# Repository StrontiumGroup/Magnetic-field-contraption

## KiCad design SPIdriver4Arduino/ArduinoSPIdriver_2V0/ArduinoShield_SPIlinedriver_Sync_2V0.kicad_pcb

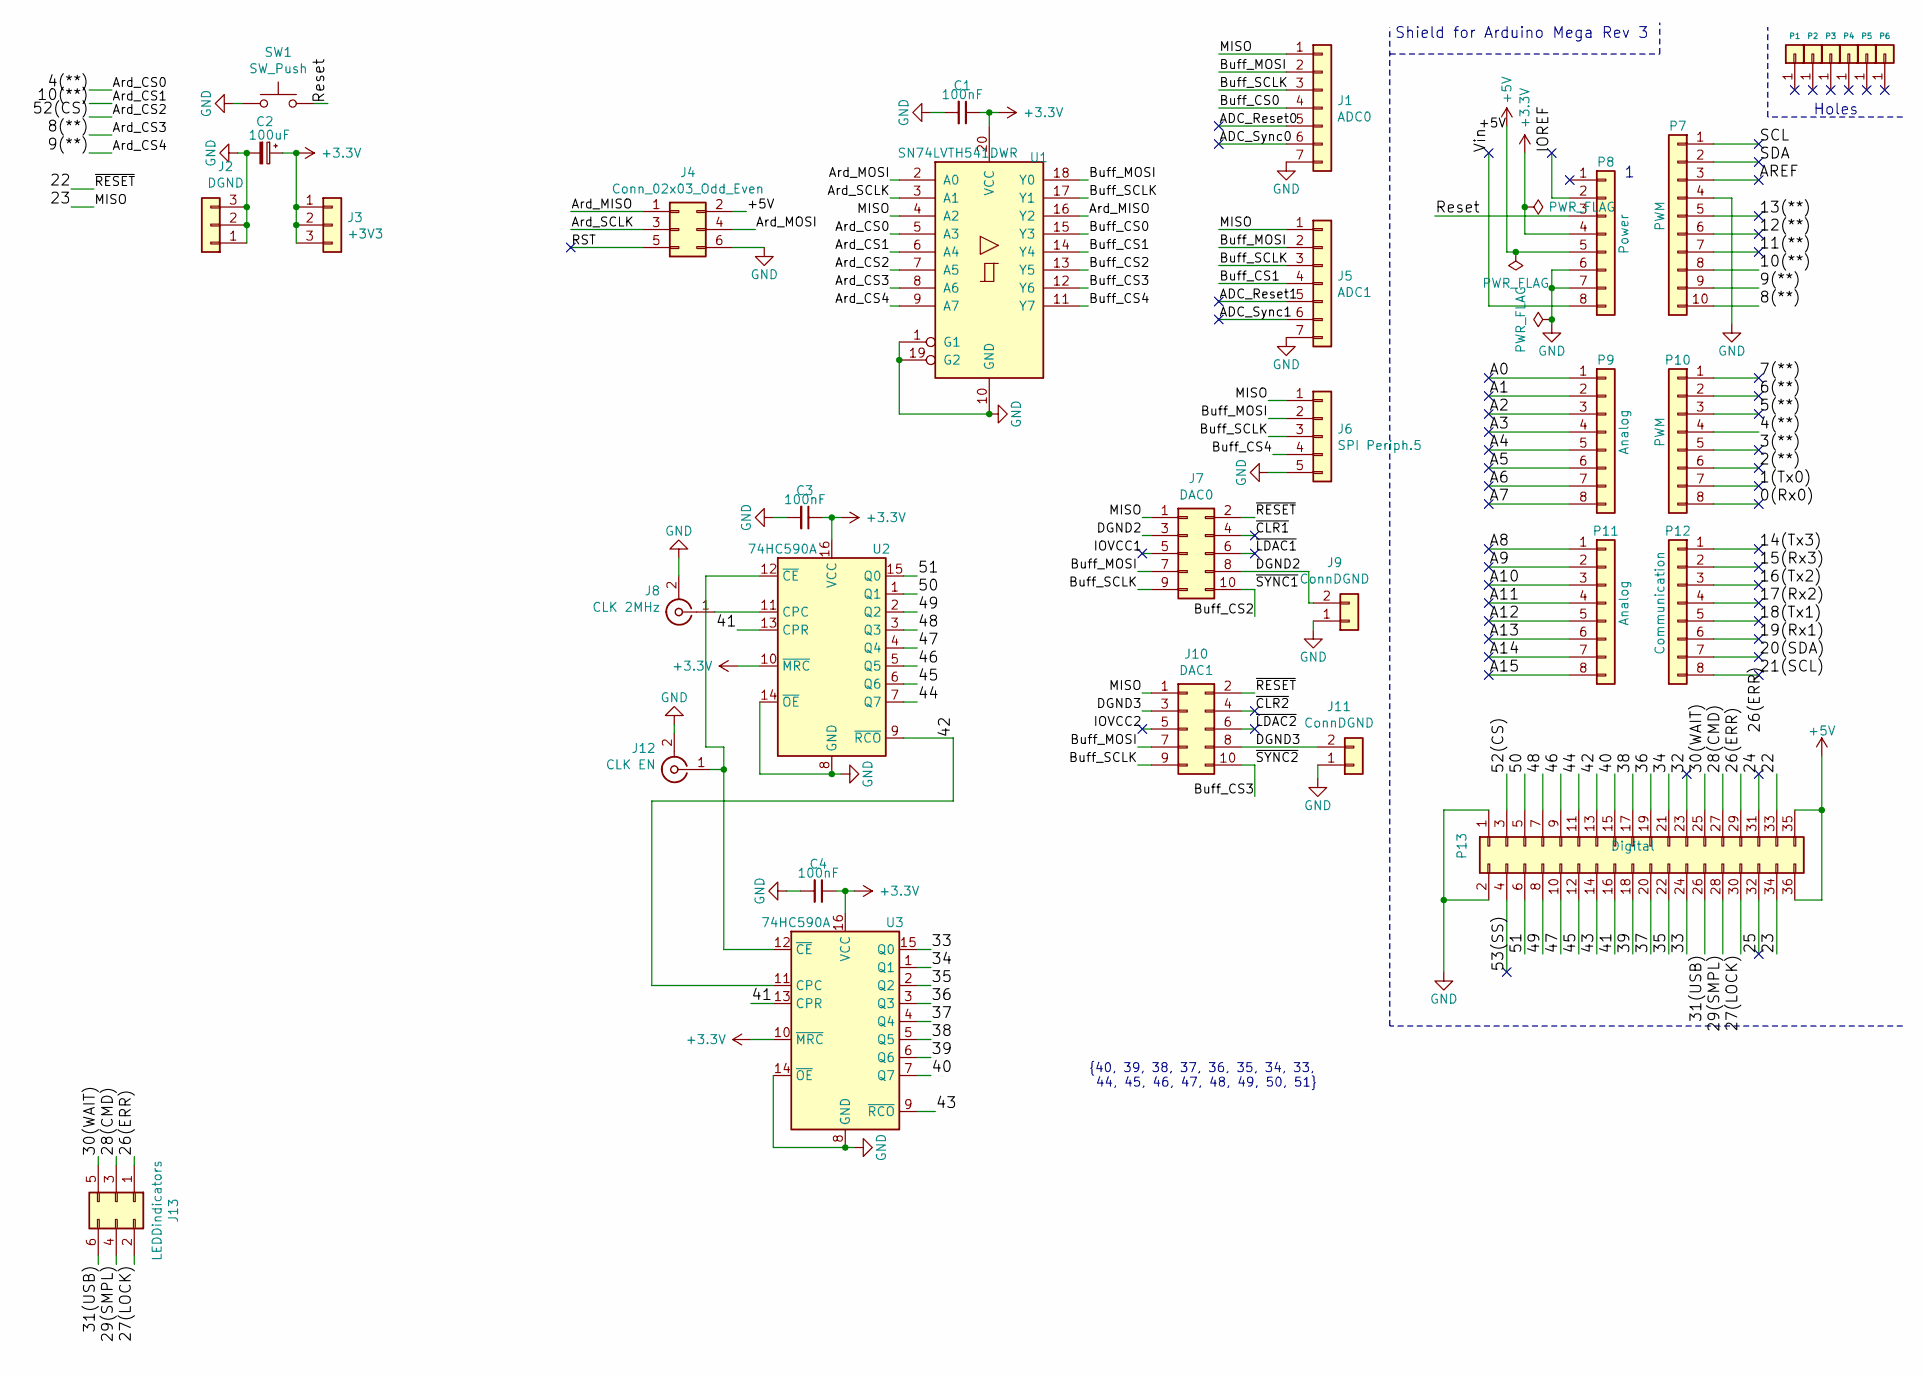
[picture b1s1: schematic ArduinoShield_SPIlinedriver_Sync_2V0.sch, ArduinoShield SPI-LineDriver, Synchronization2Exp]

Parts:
C1, C3, C4: 100nF; C_0805_2012Metric; DigiKey 399-1170-2-ND
C2: 100uF; CP_Radial_D5.0mm_P2.00mm; DigiKey 399-15740-ND
J1: ADC0; Molex_Micro-Latch_53253-0770_1x07_P2.00mm_Vertical; DigiKey WM24307-ND
J2: DGND; PinSocket_1x03_P2.54mm_Vertical
J3: +3V3; PinSocket_1x03_P2.54mm_Vertical
J4: Conn_02x03_Odd_Even; PinSocket_2x03_P2.54mm_Vertical; DigiKey SAM9289-ND
J5: ADC1; Molex_Micro-Latch_53253-0770_1x07_P2.00mm_Vertical; DigiKey WM24307-ND
J6: SPI Periph.5; PinSocket_1x05_P2.54mm_Vertical
J7: DAC0; IDC-Header_2x05_P2.54mm_Vertical; DigiKey WM3478-ND
J8: CLK 2MHz; SMA_Amphenol_132291_Vertical; DigiKey ACX1976-ND
J9, J11: ConnDGND; PinHeader_1x02_P2.54mm_Vertical
J10: DAC1; IDC-Header_2x05_P2.54mm_Vertical; DigiKey WM3478-ND
J12: CLK EN; SMA_Amphenol_132291_Vertical; DigiKey ACX1976-ND
J13: LEDDindicators; IDC-Header_2x03_P2.54mm_Vertical; DigiKey 732-5394-ND
P1, P2, P3, P4, P5, P6: CONN_01X01; Arduino_1pin
P7: PWM; Socket_Strip_Arduino_1x10
P8: Power; Socket_Strip_Arduino_1x08
P9, P11: Analog; Socket_Strip_Arduino_1x08
P10: PWM; Socket_Strip_Arduino_1x08
P12: Communication; Socket_Strip_Arduino_1x08
P13: Digital; Socket_Strip_Arduino_2x18
SW1: SW_Push; SW_SPST_TL3305A; DigiKey LL3301FF065QJ-ND
U1: SN74LVTH541DWR; SOIC-20W_7.5x12.8mm_P1.27mm; DigiKey 296-36417-1-ND
U2, U3: 74HC590A; SOIC-16_3.9x9.9mm_P1.27mm; DigiKey 296-17132-1-ND

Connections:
+3V3: C1.1, C2.1, C3.1, C4.1, J3.1, J3.2, J3.3, P8.4, U1.20 (VCC), U2.10 (~MRC), U2.16 (VCC), U3.10 (~MRC), U3.16 (VCC)
+5V: J4.2, P8.5, P13.35, P13.36
/0(Rx0): P10.8
/1(Tx0): P10.7
/2(**): P10.6
/3(**): P10.5
/4(**): P10.4, U1.5 (A3)
/5(**): P10.3
/6(**): P10.2
/7(**): P10.1
/8(**): P7.10, U1.8 (A6)
/9(**): P7.9, U1.9 (A7)
/10(**): P7.8, U1.6 (A4)
/11(**): P7.7
/12(**): P7.6
/13(**): P7.5
/14(Tx3): P12.1
/15(Rx3): P12.2
/16(Tx2): P12.3
/17(Rx2): P12.4
/18(Tx1): P12.5
/19(Rx1): P12.6
/20(SDA): P12.7
/21(SCL): P12.8
/22: J7.2, J10.2, P13.33
/23: J1.1, J5.1, J6.1, J7.1, J10.1, P13.34, U1.4 (A2)
/24: P13.31
/25: P13.32
/26(ERR): J13.1, P13.29
/27(LOCK): J13.2, P13.30
/28(CMD): J13.3, P13.27
/29(SMPL): J13.4, P13.28
/30(WAIT): J13.5, P13.25
/31(USB): J13.6, P13.26
/32: P13.23
/33: P13.24, U3.15 (Q0)
/34: P13.21, U3.1 (Q1)
/35: P13.22, U3.2 (Q2)
/36: P13.19, U3.3 (Q3)
/37: P13.20, U3.4 (Q4)
/38: P13.17, U3.5 (Q5)
/39: P13.18, U3.6 (Q6)
/40: P13.15, U3.7 (Q7)
/41: P13.16, U2.13 (CPR), U3.13 (CPR)
/42: P13.13, U2.9 (~RCO), U3.11 (CPC)
/43: P13.14, U3.9 (~RCO)
/44: P13.11, U2.7 (Q7)
/45: P13.12, U2.6 (Q6)
/46: P13.9, U2.5 (Q5)
/47: P13.10, U2.4 (Q4)
/48: P13.7, U2.3 (Q3)
/49: P13.8, U2.2 (Q2)
/50: P13.5, U2.1 (Q1)
/51: P13.6, U2.15 (Q0)
/52(CS): P13.3, U1.7 (A5)
/53(SS): P13.4
/A0: P9.1
/A1: P9.2
/A2: P9.3
/A3: P9.4
/A4: P9.5
/A5: P9.6
/A6: P9.7
/A7: P9.8
/A8: P11.1
/A9: P11.2
/A10: P11.3
/A11: P11.4
/A12: P11.5
/A13: P11.6
/A14: P11.7
/A15: P11.8
/ADC_Reset0: J1.5
/ADC_Reset1: J5.5
/ADC_Sync0: J1.6
/ADC_Sync1: J5.6
/AREF: P7.3
/Ard_MISO: J4.1, U1.16 (Y2)
/Ard_MOSI: J4.4, U1.2 (A0)
/Ard_SCLK: J4.3, U1.3 (A1)
/Buff_CS0: J1.4, U1.15 (Y3)
/Buff_CS1: J5.4, U1.14 (Y4)
/Buff_CS2: J7.10, U1.13 (Y5)
/Buff_CS3: J10.10, U1.12 (Y6)
/Buff_CS4: J6.4, U1.11 (Y7)
/Buff_MOSI: J1.2, J5.2, J6.2, J7.7, J10.7, U1.18 (Y0)
/Buff_SCLK: J1.3, J5.3, J6.3, J7.9, J10.9, U1.17 (Y1)
/DGND2: J7.3, J7.8, J9.2
/DGND3: J10.3, J10.8, J11.2
/IOREF: P8.2
/IOVCC1: J7.5
/IOVCC2: J10.5
/RST: J4.5
/Reset: P8.3, SW1.2
/SCL: P7.1
/SDA: P7.2
/Vin: P8.8
/~CLR1: J7.4
/~CLR2: J10.4
/~LDAC1: J7.6
/~LDAC2: J10.6
GND: C1.2, C2.2, C3.2, C4.2, J1.7, J2.1, J2.2, J2.3, J4.6, J5.7, J6.5, J8.2 (Ext), J9.1, J11.1, J12.2 (Ext), P7.4, P8.6, P8.7, P13.1, P13.2, SW1.1, U1.1 (G1), U1.10 (GND), U1.19 (G2), U2.8 (GND), U2.14 (~OE), U3.8 (GND), U3.14 (~OE)
unnamed: J8.1 (In), U2.11 (CPC)
unnamed: J12.1 (In), U2.12 (~CE), U3.12 (~CE)

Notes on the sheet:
Shield for Arduino Mega Rev 3
Holes
{40, 39, 38, 37, 36, 35, 34, 33, 44, 45, 46, 47, 48, 49, 50, 51}

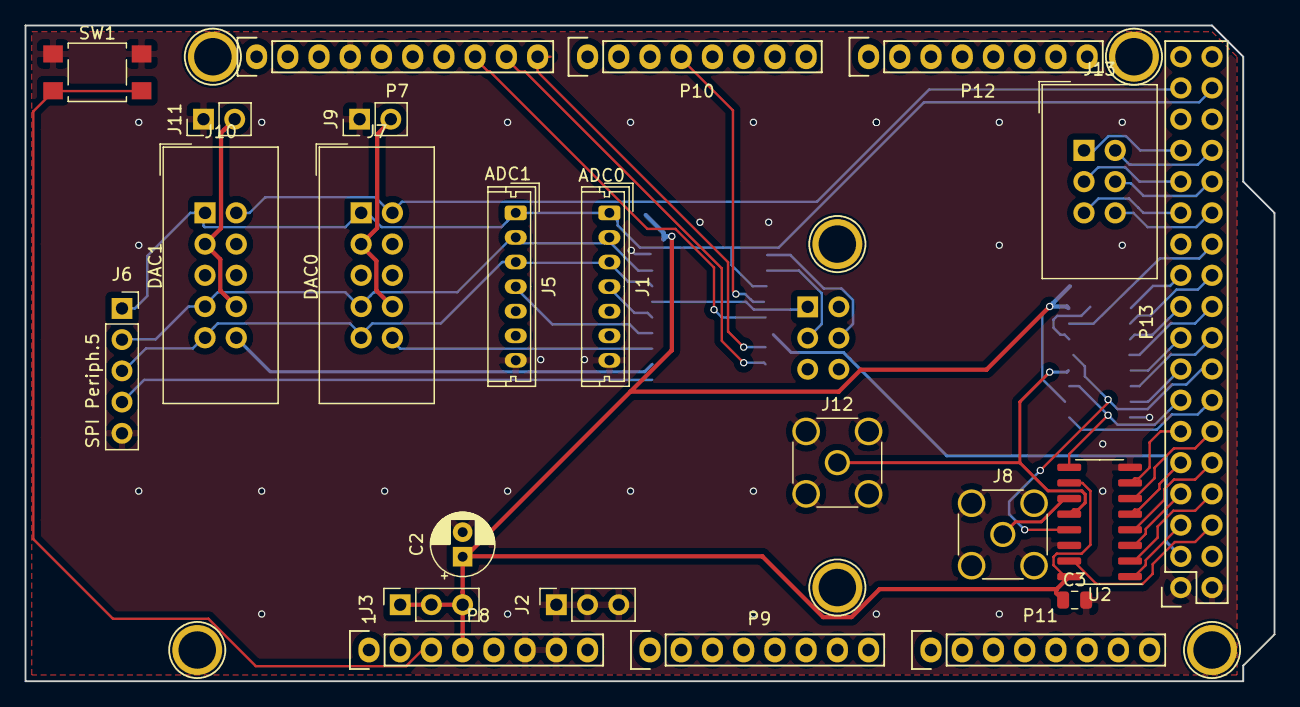
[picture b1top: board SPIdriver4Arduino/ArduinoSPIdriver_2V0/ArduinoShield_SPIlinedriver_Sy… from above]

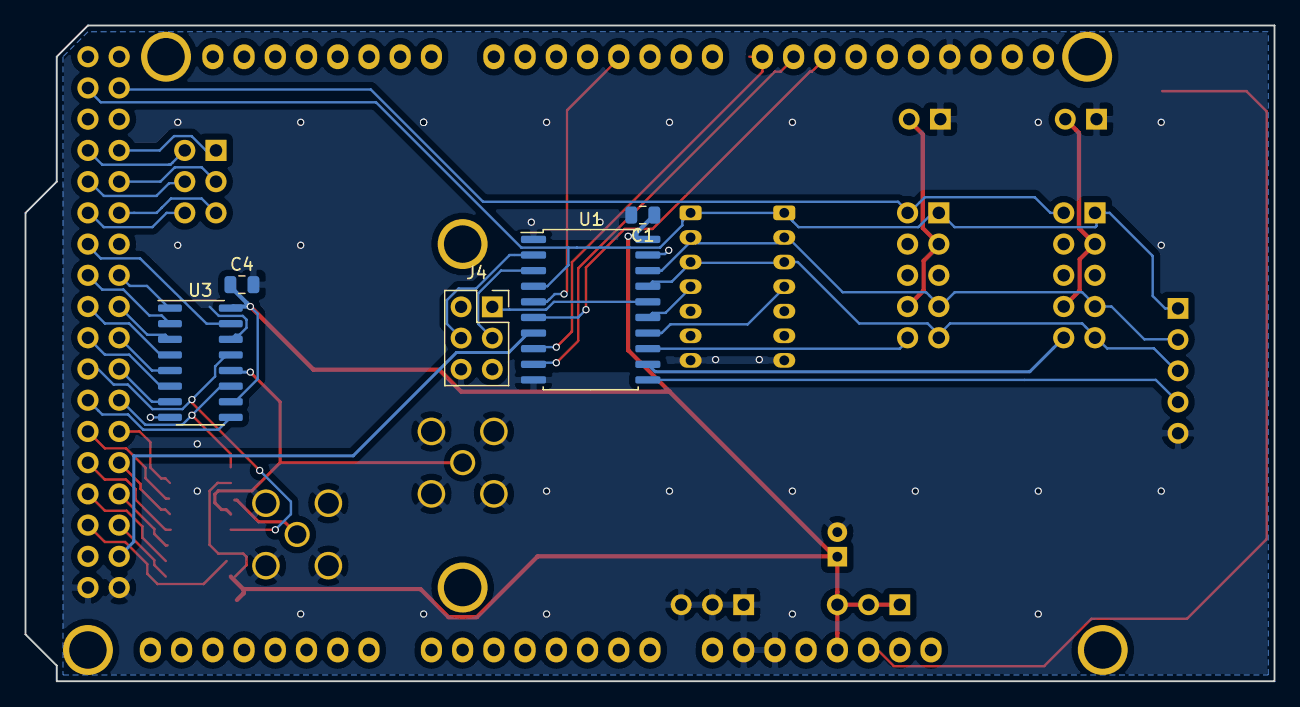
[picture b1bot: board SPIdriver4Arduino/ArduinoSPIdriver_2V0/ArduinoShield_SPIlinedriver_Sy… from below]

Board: 2 copper layers, 101.6 x 53.3 mm, 34 parts (5 on the bottom side), 50 nets.

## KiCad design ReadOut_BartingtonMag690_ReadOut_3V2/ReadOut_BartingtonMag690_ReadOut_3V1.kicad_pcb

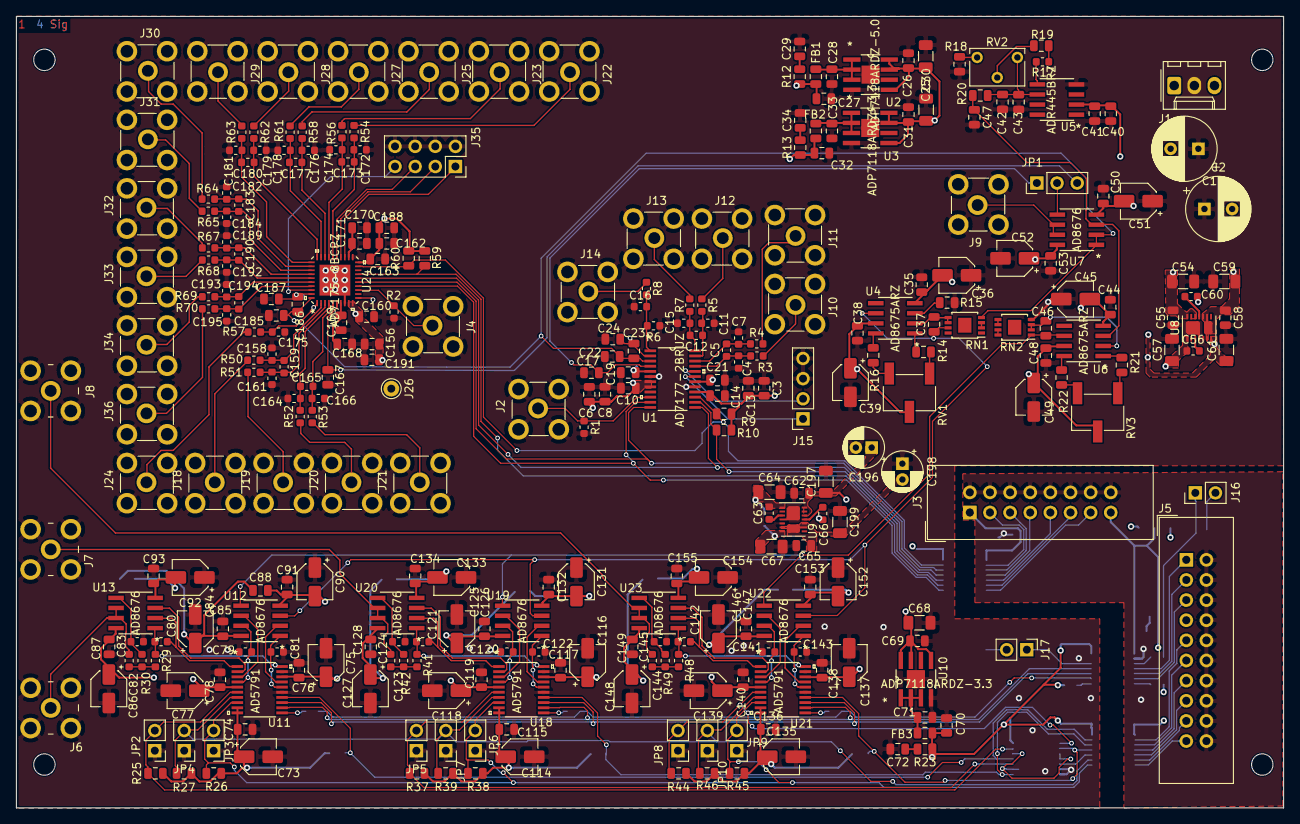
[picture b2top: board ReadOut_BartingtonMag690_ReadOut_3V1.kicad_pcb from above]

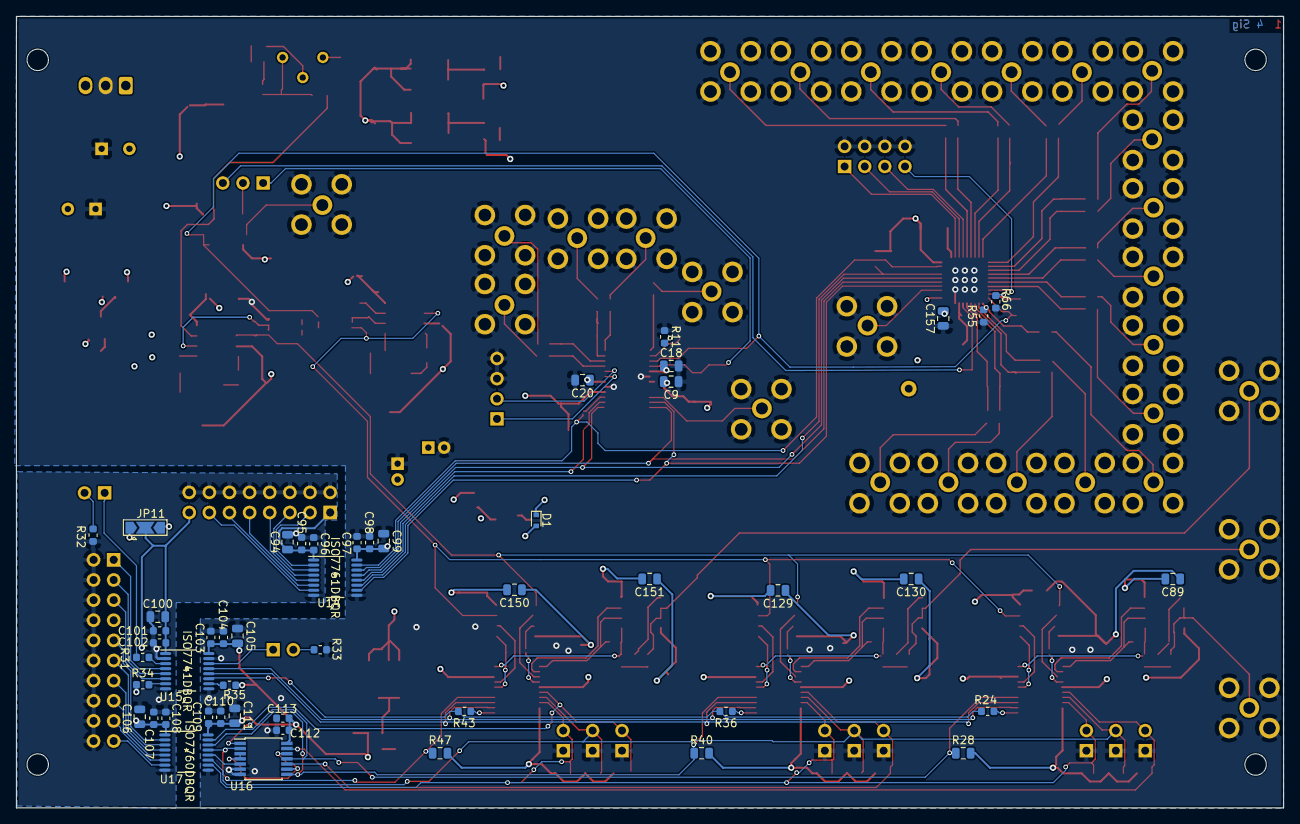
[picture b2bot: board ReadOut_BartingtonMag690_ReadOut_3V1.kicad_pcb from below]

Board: 4 copper layers, 159.9 x 99.9 mm, 353 parts (49 on the bottom side), 184 nets.

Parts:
C1, C2: 330uF; CP_Radial_D8.0mm_P3.50mm
C3, C6, C47, C94, C99, C100, C105, C106, C111, C188, C191: 10uF; C_0805_2012Metric
C4, C7, C11, C15, C16, C158, C161, C164, C166, C172, C174, C175, C176, C178, C179, C181, C182, C184, C189, C192, C193, C195: 270pF; C_0603_1608Metric
C5, C12, C159, C165, C173, C177, C180, C183, C190, C194: 680pF; C_0603_1608Metric
C8, C13, C18, C20, C72, C156, C162, C168, C170: 1uF; C_0805_2012Metric
C9, C10, C14, C17, C19, C21, C22, C23, C24, C27, C29, C32, C34, C35, C37, C38, C41, C43, C44, C46, C48, C50, C53, C70, C74, C76, C78, C85, C87, C88, C89, C91, C93, C115, C117, C119, C126, C128, C129, C130, C132, C134, C136, C138, C140, C147, C149, C150, C151, C153, C155, C157, C160, C163, C167, C169, C171, C185, C186, C187: 100nF; C_0805_2012Metric
C25, C30, C54, C57, C59, C61, C64, C67, C68, C197, C199: 10uF; C_1206_3216Metric
C26, C28, C31, C33, C55, C58, C62, C65, C69, C71: 2.2uF; C_0805_2012Metric
C36, C39, C45, C49, C51, C52, C73, C75, C77, C84, C86, C90, C92, C114, C116, C118, C125, C127, C131, C133, C135, C137, C139, C146, C148, C152, C154: 10uF; CP_Elec_4x5.8
C40, C42: 4.7uF; C_0805_2012Metric
C56, C60, C63, C66: 10nF; C_0603_1608Metric
C79, C81, C120, C122, C141, C143: 220pF; C_0603_1608Metric
C80, C121, C142: 10p; C_0603_1608Metric
C82, C123, C144: 6.2n; C_0603_1608Metric
C83, C124, C145: 620p; C_0603_1608Metric
C95, C98, C101, C104, C107, C110, C113: 1uF; C_0603_1608Metric
C96, C97, C102, C103, C108, C109, C112: 100nF; C_0603_1608Metric
C196, C198: 47uF; CP_Radial_D5.0mm_P2.00mm
D1: D_Schottky; D_SOD-523
FB1, FB2, FB3: 1k; L_0805_2012Metric
J1: INpower; Molex_KK-254_AE-6410-03A_1x03_P2.54mm_Vertical
J2: MCLK_ADC32; RF_SMB_jack_Vertical
J3: SPI0; IDC-Header_2x08_P2.54mm_Vertical
J4: MCLK_ADC24; RF_SMB_jack_Vertical
J5: SPI1; IDC-Header_2x10_P2.54mm_Vertical
J6: AnalogOut_DAC1; RF_SMA_RightAngle_5-1814400-1
J7: AnalogOut_DAC2; RF_SMA_RightAngle_5-1814400-1
J8: AnalogOut_DAC3; RF_SMA_RightAngle_5-1814400-1
J9: REFbuf_ADC; RF_SMB_jack_Vertical
J10: AIN0_ADC32; RF_SMB_jack_Vertical
J11: AIN1_ADC32; RF_SMB_jack_Vertical
J12: AIN2_ADC32; RF_SMB_jack_Vertical
J13: AIN3_ADC32; RF_SMB_jack_Vertical
J14: AIN4_ADC32; RF_SMB_jack_Vertical
J15: GPIO_ADC32; PinSocket_1x04_P2.54mm_Vertical
J16, J17: GPIx; PinHeader_1x02_P2.54mm_Vertical
J18: AIN0_ADC24; RF_SMB_jack_Vertical
J19: AIN1_ADC24; RF_SMB_jack_Vertical
J20: AIN2_ADC24; RF_SMB_jack_Vertical
J21: AIN3_ADC24; RF_SMB_jack_Vertical
J22: AIN4_ADC24; RF_SMB_jack_Vertical
J23: AIN5_ADC24; RF_SMB_jack_Vertical
J24: AIN16_ADC24; RF_SMB_jack_Vertical
J25: AIN6_ADC24; RF_SMB_jack_Vertical
J26: PDSW_ADC24; Pin_D1.0mm_L10.0mm
J27: AIN7_ADC24; RF_SMB_jack_Vertical
J28: AIN8_ADC24; RF_SMB_jack_Vertical
J29: AIN9_ADC24; RF_SMB_jack_Vertical
J30: AIN10_ADC24; RF_SMB_jack_Vertical
J31: AIN11_ADC32; RF_SMB_jack_Vertical
J32: AIN12_ADC24; RF_SMB_jack_Vertical
J33: AIN13_ADC24; RF_SMB_jack_Vertical
J34: AIN14_ADC24; RF_SMB_jack_Vertical
J35: GPIO_ADC24; PinSocket_2x04_P2.54mm_Vertical
J36: AIN15_ADC24; RF_SMB_jack_Vertical
JP1: Sel Vref; PinHeader_1x03_P2.54mm_Vertical
JP2, JP5, JP8: RESET_man; PinHeader_1x02_P2.54mm_Vertical
JP3, JP6, JP9: LDAC_man; PinHeader_1x02_P2.54mm_Vertical
JP4, JP7, JP10: CLR_man; PinHeader_1x02_P2.54mm_Vertical
JP11: PWR_single_MCU; SolderJumper-3_P2.0mm_Open_TrianglePad1.0x1.5mm
MK1, MK2, MK3, MK4: Mounting_Hole_PAD; MountingHole_2.7mm
R1, R2: 50R; R_0603_1608Metric
R3, R4, R5, R7, R8, R50, R51, R52, R53, R54, R56, R57, R58, R61, R62, R63, R64, R65, R67, R68, R69, R70: 10R; R_0603_1608Metric
R6, R11, R17, R24, R31, R36, R43, R55, R66: 0R; R_0603_1608Metric
R9, R10, R59, R60: 10k; C_0805_2012Metric
R12, R13, R23: 2R; R_0805_2012Metric
R14, R16, R21, R22: 47k; R_0805_2012Metric
R15: 680R; R_0805_2012Metric
R18: 1k; R_0805_2012Metric
R19: 100k; R_0805_2012Metric
R20: 3.3k; R_0805_2012Metric
R25, R26, R27, R28, R37, R38, R39, R40, R44, R45, R46, R47: 10k; R_0805_2012Metric
R29, R41, R48: 1.2k; R_0603_1608Metric
R30, R42, R49: 33.7k; R_0603_1608Metric
R32, R33, R34, R35: 10k; R_0603_1608Metric
RN1, RN2: LT5400BIMS8E-4-PBF; MSOP-8-1EP_3x3mm_P0.65mm_EP1.68x1.88mm
RV1, RV3: 10k; Potentiometer_Bourns_3269W_Vertical
RV2: 10k; Potentiometer_Bourns_3266W_Vertical
U1: AD7177-2BRUZ
U2: ADP7118ARDZ-5.0; ADP7118ARDZ
U3, U10: ADP7118ARDZ-3.3; ADP7118ARDZ
U4, U6: AD8675ARZ
U5: ADR445BRZ; ADR445ARZ
U7, U12, U13, U19, U20, U22, U23: AD8676; AD8676ARZ
U8: LT3032-12; Linear_DE14MA
U9: LT3032-15; Linear_DE14MA
U11, U18, U21: AD5791; AD5791ARUZ
U14: ISO7761DBQR
U15: ISO7741DBQR
U16: 74HC02; TSSOP-14_4.4x5mm_P0.65mm
U17: ISO7760DBQR
U24: AD7175-8BCPZ; CP_40_14

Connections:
/ADC24bit_1/ADC24_Ain0: C158.2, C159.1, R50.2, U24.2
/ADC24bit_1/ADC24_Ain1: C159.2, C161.1, R51.2, U24.3
/ADC24bit_1/ADC24_Ain2: C164.2, C165.1, R52.2, U24.4
/ADC24bit_1/ADC24_Ain3: C165.2, C166.1, R53.2, U24.5
/ADC24bit_1/ADC24_Ain4: C172.2, C173.1, R54.2, U24.26
/ADC24bit_1/ADC24_Ain5: C173.2, C174.1, R56.2, U24.27
/ADC24bit_1/ADC24_Ain6: C176.2, C177.1, R58.2, U24.28
/ADC24bit_1/ADC24_Ain7: C177.2, C178.1, R61.2, U24.29
/ADC24bit_1/ADC24_Ain8: C179.2, C180.1, R62.2, U24.30
/ADC24bit_1/ADC24_Ain9: C180.2, C181.1, R63.2, U24.31
/ADC24bit_1/ADC24_Ain10: C182.2, C183.1, R64.2, U24.32
/ADC24bit_1/ADC24_Ain11: C183.2, C184.1, R65.2, U24.33
/ADC24bit_1/ADC24_Ain12: C189.2, C190.1, R67.2, U24.34
/ADC24bit_1/ADC24_Ain13: C190.2, C192.1, R68.2, U24.35
/ADC24bit_1/ADC24_Ain14: C193.2, C194.1, R69.2, U24.36
/ADC24bit_1/ADC24_Ain15: C194.2, C195.1, R70.2, U24.37
/ADC24bit_1/ADC24_Ain16: C175.2, R55.2, R57.2, U24.1
/ADC24bit_1/GPIO_ADC24_0: J35.1, U24.23
/ADC24bit_1/GPIO_ADC24_1: J35.3, U24.24
/ADC24bit_1/GPIO_ADC24_2: J35.5, U24.25
/ADC24bit_1/GPIO_ADC24_3: J35.7, U24.38
/ADC24bit_1/MLCK_ADC24: J4.1, R2.1, U24.13
/ADC24bit_1/REF-: C186.2, C187.1, R66.2, U24.39
/ADC32bit_1/ADC32_Ain0: C4.2, C5.1, R3.2, U1.21
/ADC32bit_1/ADC32_Ain1: C5.2, C7.1, R4.2, U1.22
/ADC32bit_1/ADC32_Ain2: C11.2, C12.1, R5.2, U1.23
/ADC32bit_1/ADC32_Ain3: C12.2, C15.1, R7.2, U1.24
/ADC32bit_1/ADC32_Ain4: C16.2, R6.2, R8.2, U1.1
/ADC32bit_1/GPIO0_ADC32: J15.1, U1.19
/ADC32bit_1/GPIO1_ADC32: J15.2, U1.20
/ADC32bit_1/MLCK_ADC32: J2.1, R1.1, U1.10
/ADC32bit_1/REF-: C23.2, C24.1, R11.2, U1.2
/DAC20bit_1/CLR_DAC20: JP4.2, JP7.2, JP10.2, R27.1, R39.1, R46.1, U11.7, U17.11, U18.7, U21.7
/DAC20bit_1/LDAC_DAC20: JP3.2, JP6.2, JP9.2, R26.1, R38.1, R45.1, U11.8, U17.10, U18.8, U21.8
/DAC20bit_1/Rfb: C80.1, R29.2, U11.20, U13.1
/DAC20bit_1/Vout: U11.2, U13.3
/DAC20bit_1/Vout_DAC20: C82.2, J6.1, U13.6, U13.7
/DAC20bit_2/Rfb: C121.1, R41.2, U18.20, U20.1
/DAC20bit_2/Vout: U18.2, U20.3
/DAC20bit_2/Vout_DAC20: C123.2, J7.1, U20.6, U20.7
/DAC20bit_3/Rfb: C142.1, R48.2, U21.20, U23.1
/DAC20bit_3/Vout: U21.2, U23.3
/DAC20bit_3/Vout_DAC20: C144.2, J8.1, U23.6, U23.7
/GND_MCU: C94.1, C95.2, C96.1, C100.1, C101.2, C102.1, C106.1, C107.2, C108.1, J3.2, J3.4, J3.6, J3.8, J3.10, J3.12, J3.14, J3.16, J5.2, J5.4, J5.6, J5.8, J5.10, J5.12, J5.14, J5.16, J5.18, J5.20, R32.2, U14.8, U15.2, U15.8, U17.8
/ISO_DAC20_1/CLR_MCU: J5.17, U17.6
/ISO_DAC20_1/CS0_DAC20: R28.1, U11.14, U16.11, U17.15
/ISO_DAC20_1/CS0_MCU: J5.9, U17.2
/ISO_DAC20_1/CS1_DAC20: R40.1, U16.8, U17.14, U18.14
/ISO_DAC20_1/CS1_MCU: J5.11, U17.3
/ISO_DAC20_1/CS2_DAC20: R47.1, U16.2, U17.13, U21.14
/ISO_DAC20_1/CS2_MCU: J5.13, U17.4
/ISO_DAC20_1/LDAC_MCU: J5.19, U17.7
/ISO_DAC20_1/MISO: R24.1, R36.1, R43.1, U15.11
/ISO_DAC20_1/MISO_MCU: J5.5, U15.6
/ISO_DAC20_1/MOSI: U11.12, U15.13, U18.12, U21.12
/ISO_DAC20_1/MOSI_MCU: J5.1, U15.4
/ISO_DAC20_1/RESET0__DAC20: JP2.2, R25.1, U11.6, U16.13
/ISO_DAC20_1/RESET1__DAC20: JP5.2, R37.1, U16.10, U18.6
/ISO_DAC20_1/RESET2__DAC20: JP8.2, R44.1, U16.1, U21.6
/ISO_DAC20_1/RESET_MCU: J5.15, U17.5
/ISO_DAC20_1/SCLK: U11.13, U15.12, U18.13, U21.13
/ISO_DAC20_1/SCLK_MCU: J5.3, U15.5
/Isolation_ADC_1/CS0: R10.1, U1.14, U14.12
/Isolation_ADC_1/CS0_MCU: J3.9, U14.5
/Isolation_ADC_1/CS1: R59.1, U14.11, U24.17
/Isolation_ADC_1/CS1_MCU: J3.11, U14.6
/Isolation_ADC_1/MISO: U1.11, U14.10, U24.14
/Isolation_ADC_1/MISO_MCU: J3.13, U14.7
/Isolation_ADC_1/MOSI: U1.12, U14.14, U24.15
/Isolation_ADC_1/MOSI_MCU: J3.5, U14.3
/Isolation_ADC_1/SCLK: U1.13, U14.13, U24.16
/Isolation_ADC_1/SCLK_MCU: J3.7, U14.4
/Isolation_ADC_1/SYNC_ADC: R9.2, R60.1, U1.15, U14.15, U24.19
/Isolation_ADC_1/SYNC_MCU: J3.3, U14.2
/POWER_AD717x/PWR+5AVDD1: C6.1, C8.2, C9.2, C10.2, C27.1, C156.2, C157.2, C160.1, C191.1, FB1.2, R12.1, U1.7, U1.8, U24.9, U24.10
/POWER_OpAmp1/PWR+12V: C38.1, C39.1, C40.2, C41.2, C48.1, C49.1, C52.1, C53.1, C56.1, C57.1, RV1.2, RV3.2, U4.7, U5.2, U6.7, U7.8, U8.1
/POWER_OpAmp1/PWR-12V: C35.2, C36.2, C44.2, C45.2, C50.2, C51.2, C60.1, C61.1, U4.4, U6.4, U7.4, U8.7
/PWR+3.3VIOVDD: C3.2, C13.2, C14.2, C32.1, C97.2, C98.1, C99.2, C162.2, C163.2, C188.2, FB2.2, R9.1, R10.2, R13.1, R59.2, R60.2, U1.16, U14.16, U24.20
/PWR+3.3V[1]_MCU: C94.2, C95.1, C96.2, J3.1, JP11.3, U14.1
/PWR+3.3V[2]_MCU: C100.2, C101.1, C102.2, J3.15, JP11.2, R34.1, U15.1
/PWR+3.3V[3]_MCU: C106.2, C107.1, C108.2, J5.7, JP11.1, U17.1
/PWR+16V: C1.2, C25.1, C26.1, C30.1, C31.1, C54.1, C55.1, C62.1, C68.1, C69.1, C196.1, C197.1, J1.1, U2.5, U2.7, U2.8, U3.5, U3.7, U3.8, U8.12, U8.14, U9.12, U9.14, U10.5, U10.7, U10.8
/PWR-16V: C2.2, C58.2, C59.2, C65.2, C198.2, C199.2, J1.3, U8.6, U8.9, U8.10, U9.6, U9.9, U9.10
/PowerDAC1/PWR+3.3: C70.1, C73.1, C74.1, C103.2, C104.1, C105.2, C109.2, C110.1, C111.2, C112.2, C113.1, C114.1, C115.1, C135.1, C136.1, FB3.2, R23.1, R25.2, R26.2, R27.2, R28.2, R35.2, R37.2, R38.2, R39.2, R40.2, R44.2, R45.2, R46.2, R47.2, U11.9, U11.10, U15.16, U16.14, U17.16, U18.9, U18.10, U21.9, U21.10
/PowerDAC1/PWR+15V: C63.1, C64.1, C77.1, C78.1, C84.1, C85.1, C86.1, C87.1, C88.1, C89.1, C118.1, C119.1, C125.1, C126.1, C127.1, C128.1, C129.1, C130.1, C139.1, C140.1, C146.1, C147.1, C148.1, C149.1, C150.1, C151.1, D1.1, U9.1, U11.5, U12.8, U13.8, U18.5, U19.8, U20.8, U21.5, U22.8, U23.8
/PowerDAC1/PWR-15V: C66.1, C67.1, C75.1, C76.1, C88.2, C89.2, C90.2, C91.2, C92.2, C93.2, C116.1, C117.1, C129.2, C130.2, C131.2, C132.2, C133.2, C134.2, C137.1, C138.1, C150.2, C151.2, C152.2, C153.2, C154.2, C155.2, D1.2, U9.7, U11.18, U12.4, U13.4, U18.18, U19.4, U20.4, U21.18, U22.4, U23.4
/REF+2.5V_ADC24: C167.2, JP1.3, U24.6
/REF+2.5V_ADC32: C17.2, JP1.1, U1.4
/REF+5.0V_buf: C22.1, C23.1, C185.1, C186.1, RN1.4, U1.3, U7.1, U7.2, U24.40
/REF+10.0V: C46.2, RN2.1, U6.6, U12.5, U19.5, U22.5
/REF-10.0V: C37.1, RN1.7, U4.6, U12.3, U19.3, U22.3
/VoltageRefs/REF+2.5V: JP1.2, U7.5
/VoltageRefs/REF+2.5V_buff: J9.1, U7.6, U7.7
/VoltageRefs/REF+5.0V: C42.1, C43.1, R20.2, RV2.1, U5.6
GND: C1.1, C2.1, C3.1, C4.1, C6.2, C7.2, C8.1, C9.1, C10.1, C11.1, C13.1, C14.1, C15.2, C16.1, C17.1, C18.2, C19.2, C20.2, C21.2, C22.2, C24.2, C25.2, C26.2, C27.2, C28.2, C29.2, C30.2, C31.2, C32.2, C33.2, C34.2, C35.1, C36.1, C38.2, C39.2, C40.1, C41.1, C42.2, C43.2, C44.1, C45.1, C47.2, C48.2, C49.2, C50.1, C51.1, C52.2, C53.2, C54.2, C55.2, C57.2, C58.1, C59.1, C61.2, C62.2, C64.2, C65.1, C67.2, C68.2, C69.2, C70.2, C71.2, C72.2, C73.2, C74.2, C75.2, C76.2, C77.2, C78.2, C79.1, C81.2, C83.1, C84.2, C85.2, C86.2, C87.2, C90.1, C91.1, C92.1, C93.1, C97.1, C98.2, C99.1, C103.1, C104.2, C105.1, C109.1, C110.2, C111.1, C112.1, C113.2, C114.2, C115.2, C116.2, C117.2, C118.2, C119.2, C120.1, C122.2, C124.1, C125.2, C126.2, C127.2, C128.2, C131.1, C132.1, C133.1, C134.1, C135.2, C136.2, C137.2, C138.2, C139.2, C140.2, C141.1, C143.2, C145.1, C146.2, C147.2, C148.2, C149.2, C152.1, C153.1, C154.1, C155.1, C156.1, C157.1, C158.1, C160.2, C161.2, C162.1, C163.1, C164.1, C166.2, C167.1, C168.2, C169.2, C170.2, C171.2, C172.1, C174.2, C175.1, C176.1, C178.2, C179.1, C181.2, C182.1, C184.2, C185.2, C187.2, C188.1, C189.1, C191.2, C192.2, C193.1, C195.2, C196.2, C197.2, C198.1, C199.1, J1.2, J2.2, J4.2, J6.2, J7.2, J8.2, J9.2, J10.2, J11.2, J12.2, J13.2, J14.2, J15.3, J15.4, J18.2, J19.2, J20.2, J21.2, J22.2, J23.2, J24.2, J25.2, J27.2, J28.2, J29.2, J30.2, J31.2, J32.2, J33.2, J34.2, J35.2, J35.4, J35.6, J35.8, J36.2, JP2.1, JP3.1, JP4.1, JP5.1, JP6.1, JP7.1, JP8.1, JP9.1, JP10.1, R1.2, R2.2, R6.1, R11.1, R15.2, R18.1, R33.2, R55.1, R66.1, RN2.4, U1.6, U1.17, U2.4, U2.9, U3.4, U3.9, U5.4, U8.4, U8.5, U9.4, U9.5, U10.4, U10.9, U11.15, U11.19, U14.9, U15.9, U15.15, U16.6, U16.7, U17.9, U18.15, U18.19, U21.15, U21.19, U24.8, U24.21, U24.41
unnamed: C18.1, C19.1, U1.5
unnamed: C20.1, C21.1, U1.18
unnamed: C28.1, FB1.1, U2.1, U2.2, U2.3
unnamed: C29.1, R12.2
unnamed: C33.1, FB2.1, U3.1, U3.2, U3.3
unnamed: C34.1, R13.2
unnamed: C37.2, RN1.5, RN1.6, U4.2
unnamed: C46.1, RN2.2, RN2.3, U6.2
unnamed: C47.1, R20.1, U6.3, U7.3
unnamed: C56.2, U8.3
unnamed: C60.2, U8.11
unnamed: C63.2, U9.3
unnamed: C66.2, U9.11
unnamed: C71.1, FB3.1, U10.1, U10.2, U10.3
unnamed: C72.1, R23.2
unnamed: C79.2, U11.4, U12.7
unnamed: C80.2, U11.1, U13.2
unnamed: C81.1, U11.16, U12.1
unnamed: C82.1, R29.1, R30.2
unnamed: C83.2, R30.1, U13.5
unnamed: C120.2, U18.4, U19.7
unnamed: C121.2, U18.1, U20.2
unnamed: C122.1, U18.16, U19.1
unnamed: C123.1, R41.1, R42.2
unnamed: C124.2, R42.1, U20.5
unnamed: C141.2, U21.4, U22.7
unnamed: C142.2, U21.1, U23.2
unnamed: C143.1, U21.16, U22.1
unnamed: C144.1, R48.1, R49.2
unnamed: C145.2, R49.1, U23.5
unnamed: C168.1, C169.1, U24.7
unnamed: C170.1, C171.1, U24.22
unnamed: J10.1, R3.1
unnamed: J11.1, R4.1
unnamed: J12.1, R5.1
unnamed: J13.1, R7.1
unnamed: J14.1, R8.1
unnamed: J16.1, R31.1
unnamed: J16.2, R32.1
unnamed: J17.1, U15.14
unnamed: J17.2, R33.1
unnamed: J18.1, R50.1
unnamed: J19.1, R51.1
unnamed: J20.1, R52.1
unnamed: J21.1, R53.1
unnamed: J22.1, R54.1
unnamed: J23.1, R56.1
unnamed: J24.1, R57.1
unnamed: J25.1, R58.1
unnamed: J26.1, U24.11
unnamed: J27.1, R61.1
unnamed: J28.1, R62.1
unnamed: J29.1, R63.1
unnamed: J30.1, R64.1
unnamed: J31.1, R65.1
unnamed: J32.1, R67.1
unnamed: J33.1, R68.1
unnamed: J34.1, R69.1
unnamed: J36.1, R70.1
unnamed: R14.1, RV1.1
unnamed: R14.2, U4.1
unnamed: R15.1, U4.3
unnamed: R16.1, RV1.3
unnamed: R16.2, U4.8
unnamed: R17.1, U5.5
unnamed: R17.2, R19.1
unnamed: R18.2, RV2.3
unnamed: R19.2, RV2.2
unnamed: R21.1, RV3.1
unnamed: R21.2, U6.1
unnamed: R22.1, RV3.3
unnamed: R22.2, U6.8
unnamed: R24.2, U11.11
unnamed: R31.2, U15.3
unnamed: R34.2, U15.7
unnamed: R35.1, U15.10
unnamed: R36.2, U18.11
unnamed: R43.2, U21.11
unnamed: RN1.2, RN1.3
unnamed: RN2.5, RN2.6
unnamed: RN2.7, RN2.8
unnamed: U11.3, U12.6
unnamed: U11.17, U12.2
unnamed: U16.5, U17.12
unnamed: U16.3, U16.4, U16.9, U16.12
unnamed: U18.3, U19.6
unnamed: U18.17, U19.2
unnamed: U21.3, U22.6
unnamed: U21.17, U22.2

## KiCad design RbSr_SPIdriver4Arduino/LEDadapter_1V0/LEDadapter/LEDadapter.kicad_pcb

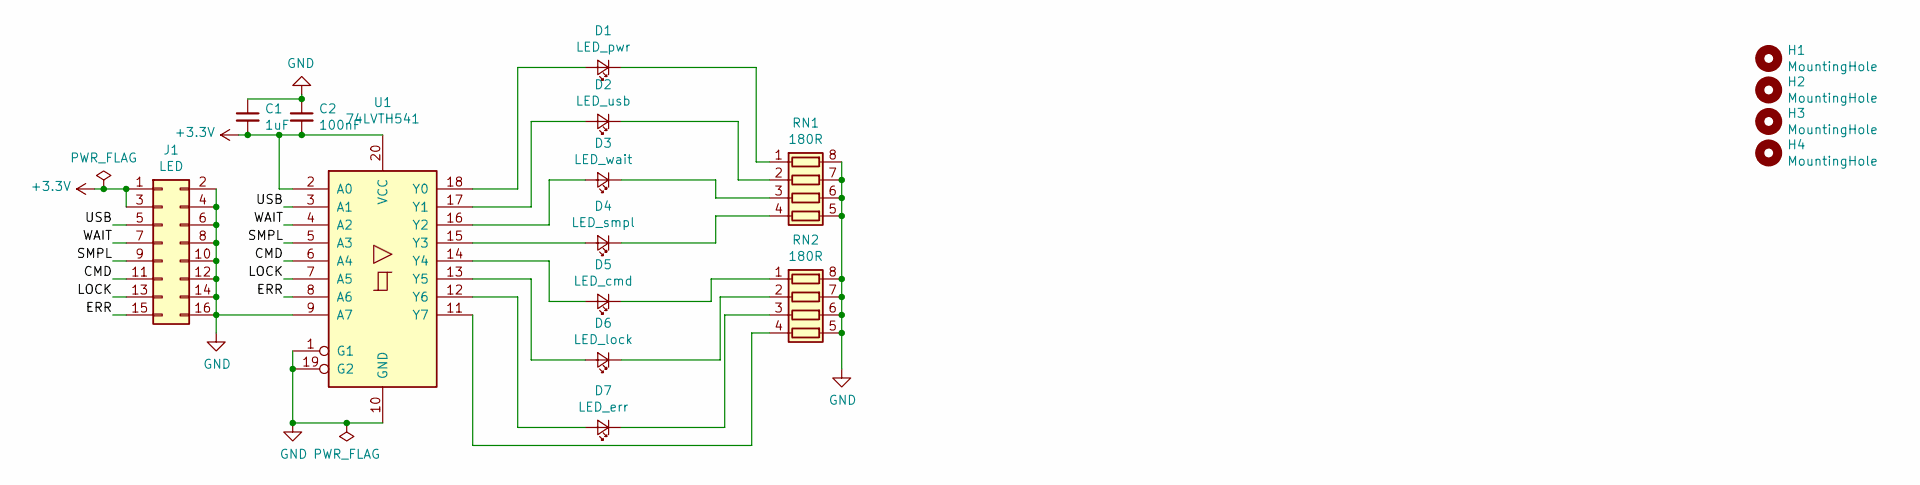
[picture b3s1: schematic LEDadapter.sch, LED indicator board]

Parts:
C1: 1uF; C_0603_1608Metric; DigiKey 732-7971-1-ND
C2: 100nF; C_0603_1608Metric; DigiKey 732-7989-1-ND
D1: LED_pwr; LED_0603_1608Metric; DigiKey 732-4980-1-ND
D2: LED_usb; LED_0603_1608Metric; DigiKey 732-4980-1-ND
D3: LED_wait; LED_0603_1608Metric; DigiKey 732-4980-1-ND
D4: LED_smpl; LED_0603_1608Metric; DigiKey 732-4980-1-ND
D5: LED_cmd; LED_0603_1608Metric; DigiKey 732-4980-1-ND
D6: LED_lock; LED_0603_1608Metric; DigiKey 732-4980-1-ND
D7: LED_err; LED_0603_1608Metric; DigiKey 732-4978-1-ND
H1, H2, H3, H4: MountingHole; MountingHole_2.7mm_Pad
J1: LED; IDC-Header_2x08_P2.54mm_Vertical; DigiKey 609-3641-ND
RN1, RN2: 180R; R_Array_Concave_4x0402; DigiKey Y7181CT-ND
U1: 74LVTH541; TSSOP-20_4.4x6.5mm_P0.65mm; DigiKey 296-8729-1-ND

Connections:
+3V3: C1.2, C2.2, J1.1, J1.3, U1.2 (A0), U1.20 (VCC)
/CMD: J1.11, U1.6 (A4)
/ERR: J1.15, U1.8 (A6)
/LOCK: J1.13, U1.7 (A5)
/SMPL: J1.9, U1.5 (A3)
/USB: J1.5, U1.3 (A1)
/WAIT: J1.7, U1.4 (A2)
GND: C1.1, C2.1, J1.2, J1.4, J1.6, J1.8, J1.10, J1.12, J1.14, J1.16, RN1.5 (R4.2), RN1.6 (R3.2), RN1.7 (R2.2), RN1.8 (R1.2), RN2.5 (R4.2), RN2.6 (R3.2), RN2.7 (R2.2), RN2.8 (R1.2), U1.1 (G1), U1.9 (A7), U1.10 (GND), U1.19 (G2)
unnamed: D1.1 (K), RN1.1 (R1.1)
unnamed: D1.2 (A), U1.18 (Y0)
unnamed: D2.1 (K), RN1.2 (R2.1)
unnamed: D2.2 (A), U1.17 (Y1)
unnamed: D3.1 (K), RN1.3 (R3.1)
unnamed: D3.2 (A), U1.16 (Y2)
unnamed: D4.1 (K), RN1.4 (R4.1)
unnamed: D4.2 (A), U1.15 (Y3)
unnamed: D5.1 (K), RN2.1 (R1.1)
unnamed: D5.2 (A), U1.14 (Y4)
unnamed: D6.1 (K), RN2.2 (R2.1)
unnamed: D6.2 (A), U1.13 (Y5)
unnamed: D7.1 (K), RN2.3 (R3.1)
unnamed: D7.2 (A), U1.12 (Y6)
unnamed: RN2.4 (R4.1), U1.11 (Y7)

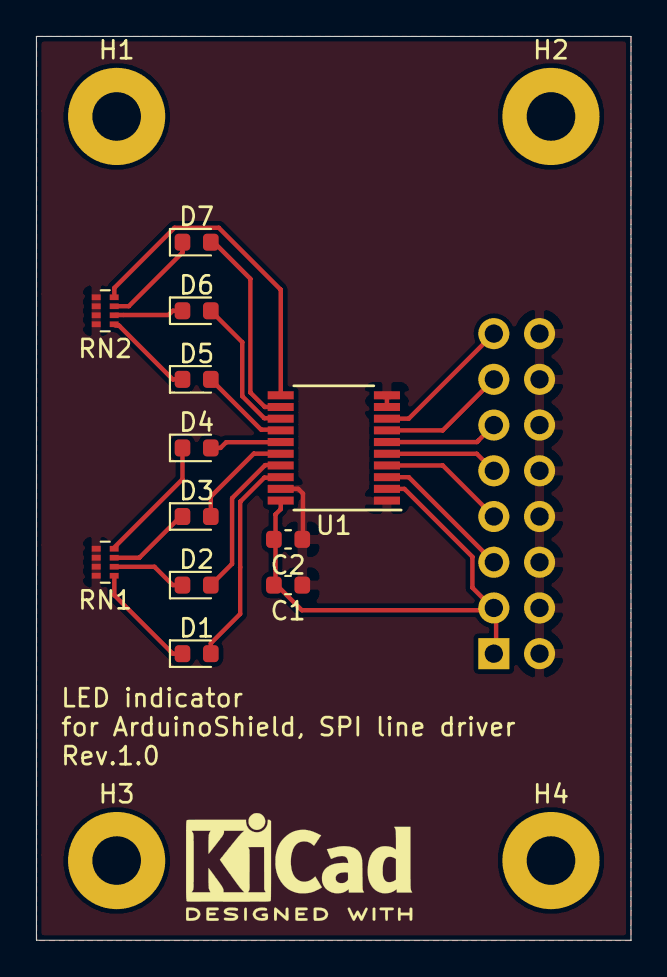
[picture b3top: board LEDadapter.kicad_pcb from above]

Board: 2 copper layers, 33.0 x 50.2 mm, 17 parts (1 on the bottom side), 23 nets.

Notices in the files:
parts and their libraries:
Copyright 2016 Accelerated Designs. All rights reserved.
